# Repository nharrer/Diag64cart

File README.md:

# Rev. 3

This is a fork of [Sven Petersen's excellent C64 Diagnostic Cartridge Board](https://github.com/svenpetersen1965/Diag64cart).

The only change is that JP3 is implemented as a real jumper instead of a solder bridge. That way the Cart can quickly be reconfigured to be used on a C64 and a C128 without having to cut and resolder a solder bridge. And C64 Dead Test Roms are still possible.

__Example Configuration__:

```
EEPROM
ADDRESS  SW1  SW2  ROM                  JP7     JP3
-------------------------------------------------------
C64 Mode:
$0000    OFF  OFF  Diagnostic 586220    closed  closed
$2000    ON   OFF  DeadTest 781220      closed  closed
$4000    OFF  ON   Diag 4.1.1           closed  closed
$6000    ON   ON   DeadTest STID 1.2.0  closed  closed

C128 Mode:
$8000    OFF  OFF  Diag C128 785260     open    open
$C000    OFF  ON   Diag C128 789010     open    open
```

Now follows the original README:

# Diag64cart
The Diag64cart is a C64/C128 cartridge PCB, that is especially made for the need of diagnostic software, like Dead Test Rev. 781220 and Diagnostic Rev. 586220. The Diag64cart is derived from the Versa64cart (https://github.com/bwack/Versa64Cart), it lacks of the ability to be a 16k cartridge, though.
The geometry of this cart was especially made for the cheap Maszczyk KM-20 and the Kradex Z7 cartridge cases. Those are available from https://restore-store.de/ or https://www.tme.eu.
Dead Test and Diagnostic reside in two different address spaces of the C64. Also, they are differently configured via GAME  or EXROM and use different chip select signals (ROMH or ROML).

This repository contains binary files from other projects. The sources can be found in documen 164-6-01-** or here:
1.	(Commodore) Diagnostic Rev. 586220 (C64) (Version +0.5):  http://blog.worldofjani.com/?p=164
2.	(Commodore) Dead Test Rev. 781220 (C64):  http://blog.worldofjani.com/?p=164
3.	STID Dead Test (v1.2.0): https://github.com/stid/kick-c64-dead-test
4.	(Commodore) Diagnostic Rev. 785260 (C128):  http://blog.worldofjani.com/?p=164
5.	(Commodore) Diagnostic Rev. 588121 (C128):  http://blog.worldofjani.com/?p=164
6.	1541 Diagnostic (World of Jani): : http://blog.worldofjani.com/?p=2180
7.	Diag 4.1.1.: http://blog.worldofjani.com/?p=164

BOM value (12.12.2020): 9.79€

Check out the 3D printed cartridge case from <a href="https://www.thingiverse.com/thing:4759098">retrorewind.ca</a>.

# The burn-In Software
This software requires modification of the default Configuration, since all four cartridges require EXROM=0 and Chip Select=ROML.

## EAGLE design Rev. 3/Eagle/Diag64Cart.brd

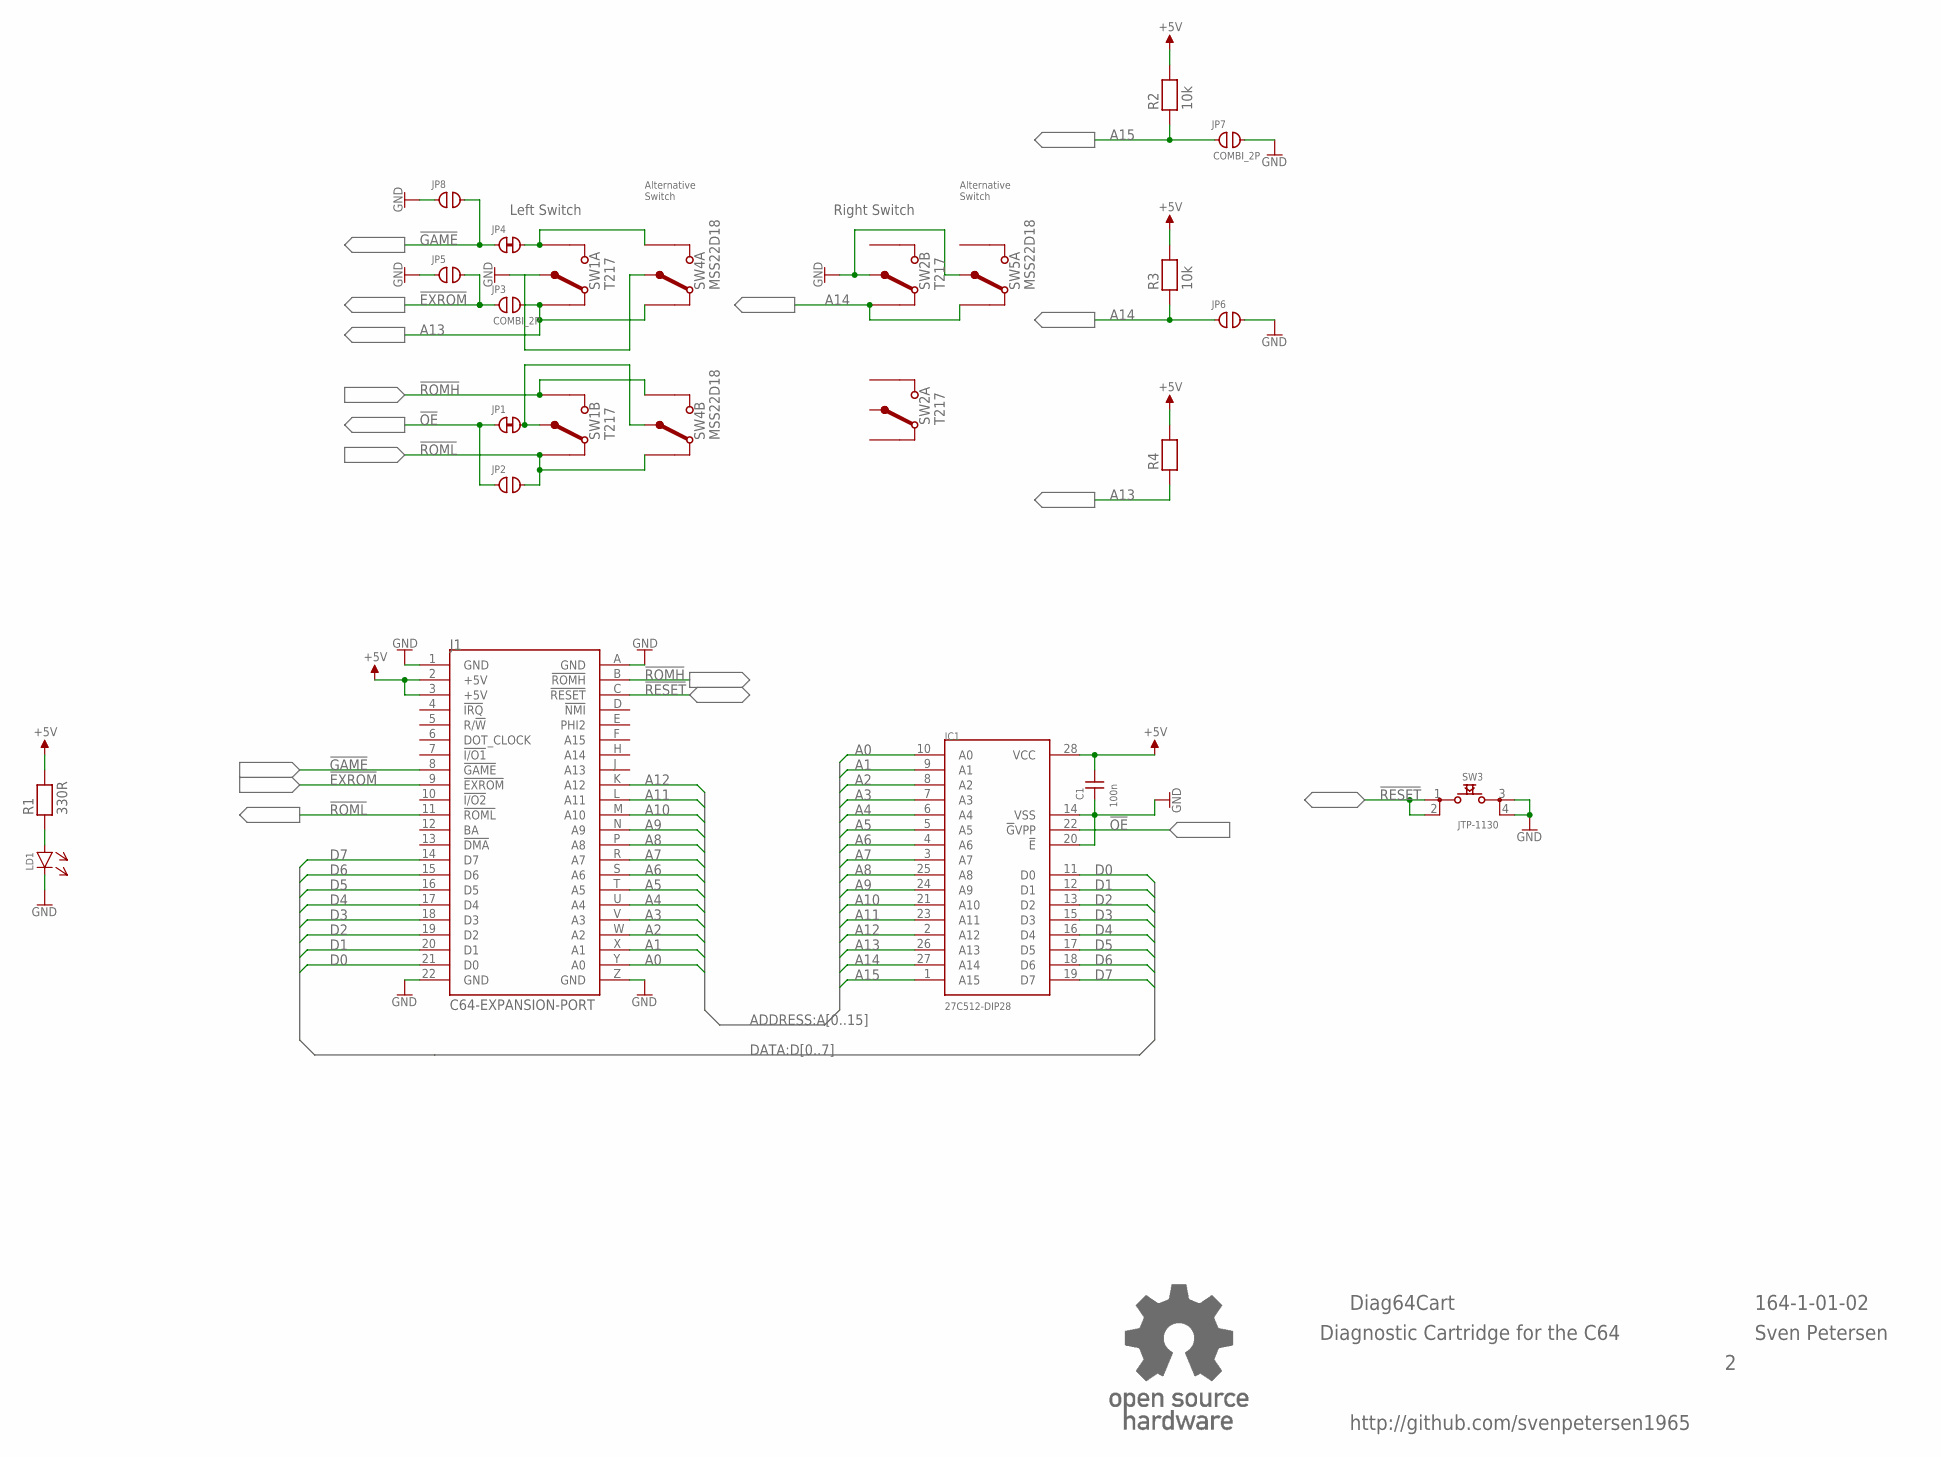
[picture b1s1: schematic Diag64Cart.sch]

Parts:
C1: 100n; C-2,5
IC1: 27C512-DIP28; DIL28-6
J1: C64-EXPANSION-PORT; EXPANSIO_SQ
JP1, JP4: CLOSED; CP_CL
JP2, JP5, JP6, JP8: OPEN; CP_OP
JP3, JP7: COMBI_2P; COMBI-2P
LD1: 3MM
R1: 330R; R-10
R2, R3, R4: 10k; R-10
SW1, SW2: T217; T217_SIDE
SW3: JTP-1130
SW4, SW5: MSS22D18; DPDT_9MM
U$43: OPEN_SOURCE_HW; OPENHW

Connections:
!EXROM: J1.9 (!EXROM), JP3.1, JP5.2
!GAME: J1.8 (!GAME), JP4.1, JP8.2
!OE: IC1.22 (!G!VPP), JP1.1, JP2.1
!RESET: J1.C (!RESET), SW3.1, SW3.2
!ROMH: J1.B (!ROMH), SW1.UP2 (UP), SW4.6 (UP)
!ROML: J1.11 (!ROML), JP2.2, SW1.DWN2 (DWN), SW4.4 (DWN)
+5V: C1.2, IC1.28 (VCC), J1.2 (+5V), J1.3 (+5V), R1.2, R2.2, R3.2, R4.2
A0: IC1.10 (A0), J1.Y (A0)
A1: IC1.9 (A1), J1.X (A1)
A2: IC1.8 (A2), J1.W (A2)
A3: IC1.7 (A3), J1.V (A3)
A4: IC1.6 (A4), J1.U (A4)
A5: IC1.5 (A5), J1.T (A5)
A6: IC1.4 (A6), J1.S (A6)
A7: IC1.3 (A7), J1.R (A7)
A8: IC1.25 (A8), J1.P (A8)
A9: IC1.24 (A9), J1.N (A9)
A10: IC1.21 (A10), J1.M (A10)
A11: IC1.23 (A11), J1.L (A11)
A12: IC1.2 (A12), J1.K (A12)
A13: IC1.26 (A13), JP3.2, R4.1, SW1.DWN1 (DWN), SW4.3 (DWN)
A14: IC1.27 (A14), JP6.1, R3.1, SW2.DWN2 (DWN), SW5.3 (DWN)
A15: IC1.1 (A15), JP7.1, R2.1
D0: IC1.11 (D0), J1.21 (D0)
D1: IC1.12 (D1), J1.20 (D1)
D2: IC1.13 (D2), J1.19 (D2)
D3: IC1.15 (D3), J1.18 (D3)
D4: IC1.16 (D4), J1.17 (D4)
D5: IC1.17 (D5), J1.16 (D5)
D6: IC1.18 (D6), J1.15 (D6)
D7: IC1.19 (D7), J1.14 (D7)
GND: C1.1, IC1.14 (VSS), IC1.20 (!E), J1.1 (GND), J1.22 (GND), J1.A (GND), J1.Z (GND), JP5.1, JP6.2, JP7.2, JP8.1, LD1.C (K), SW1.COM1 (COM), SW2.COM2 (COM), SW3.3, SW3.4, SW5.2 (COM)
unnamed: JP4.2, SW1.UP1 (UP), SW4.1 (UP)
unnamed: LD1.A, R1.1
unnamed: JP1.2, SW1.COM2 (COM), SW4.5 (COM)

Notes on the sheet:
Diag64Cart
Sven Petersen
164-1-01-02
http://github.com/svenpetersen1965
Left Switch
Right Switch
Diagnostic Cartridge for the C64
Alternative Switch

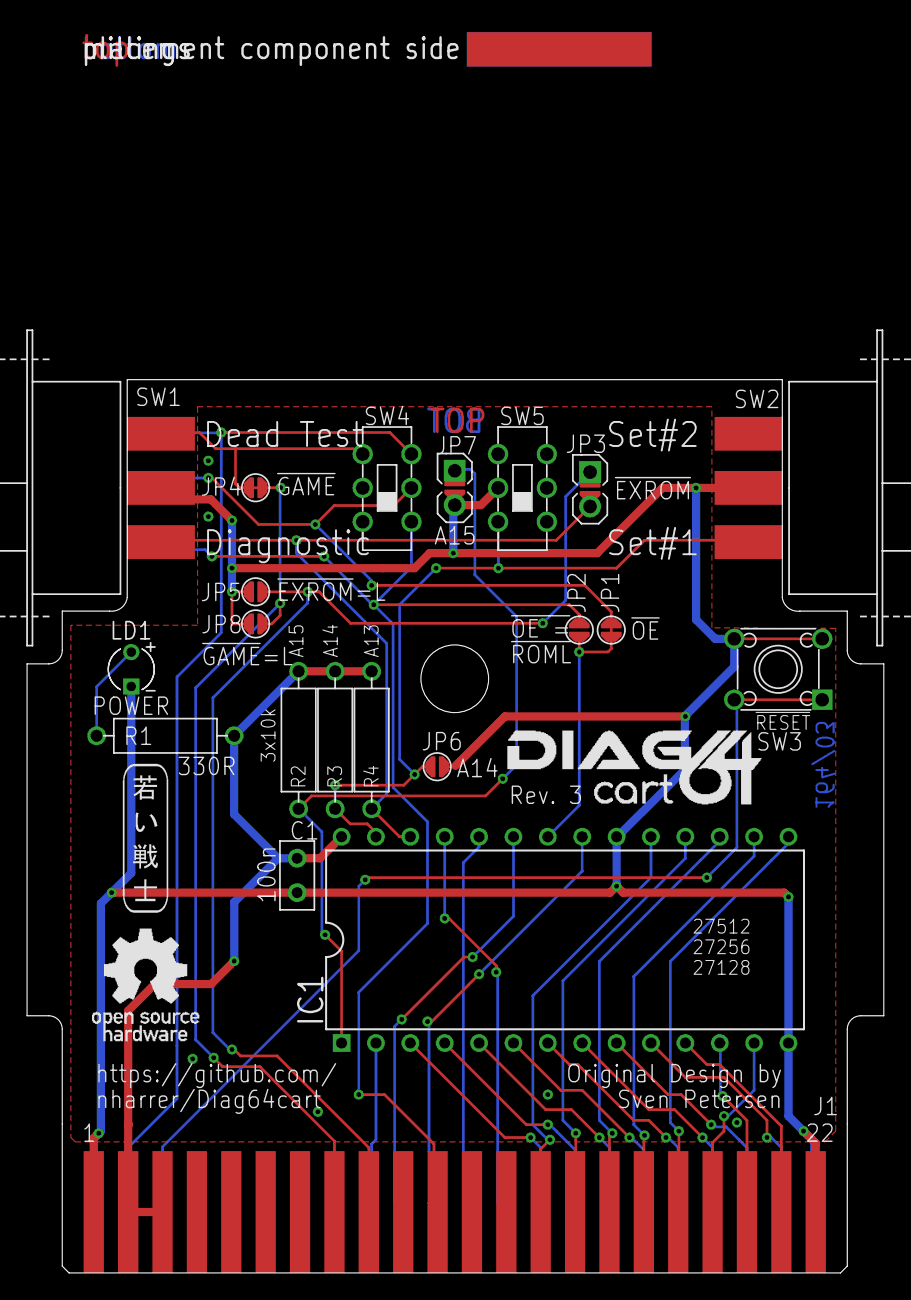
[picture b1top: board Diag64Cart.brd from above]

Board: 2 copper layers, 63.3 x 92.0 mm, 26 parts (1 on the bottom side), 35 nets.

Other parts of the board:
U$26: DIAG64CART
U$40: 2LAYER
U$41: PCB-TITLE/
U$42: SVEN_TAG

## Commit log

2022-03-02 Added Note about changes in this fork.
2022-03-02 Rev. 3 Eagle and Gerber files.
2022-03-02 Example ROM configuration
2022-03-02 Link to Github
